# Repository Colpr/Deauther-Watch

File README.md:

# Deauther-Watch
PCB, schematic and image files for the deauther watch project by Colpr on https://hackaday.io/project/193281-deauther-smart-watch-v1

##### Project is currently on version 1.

### NOTE: Please refer to the license, this project is open-source under the MIT license with all the terms and conditions.

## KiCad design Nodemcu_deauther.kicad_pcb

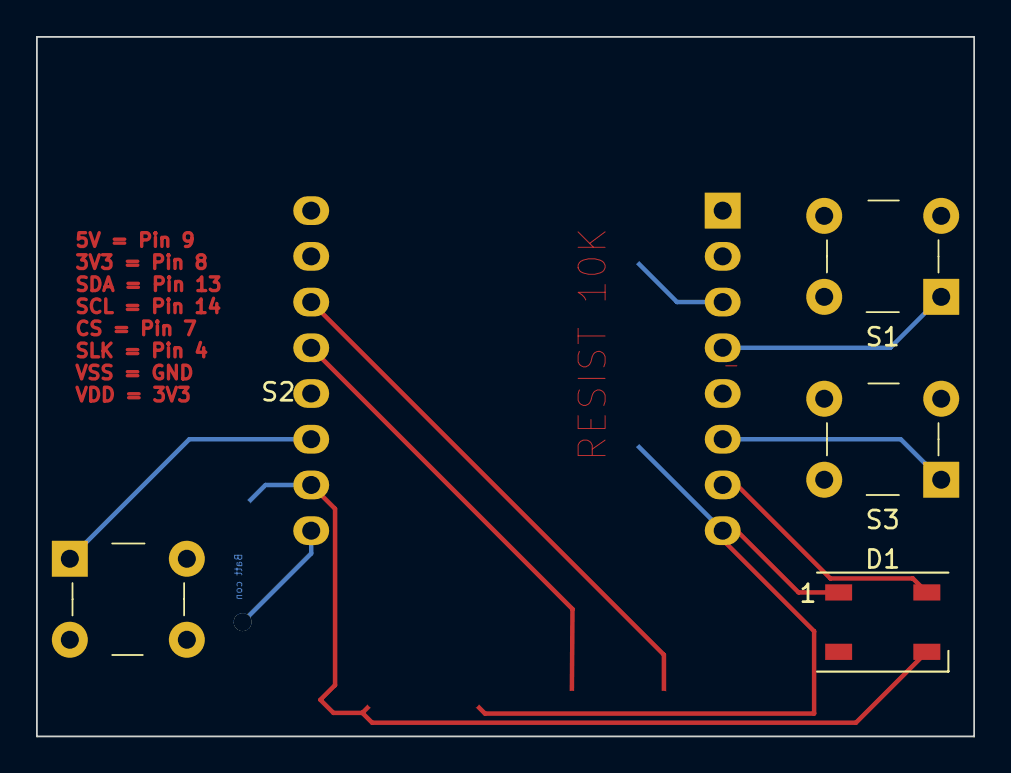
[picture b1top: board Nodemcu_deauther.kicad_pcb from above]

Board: 2 copper layers, 52.1 x 38.9 mm, 5 parts (1 on the bottom side), 6 nets.

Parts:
D1: WS2812B; LED_WS2812B_PLCC4_5.0x5.0mm_P3.2mm
S1, S2, S3: B3F-1000; Switch_Tactile_THT_B3F-1xxx
U1: WeMos_D1_mini; WEMOS_D1_mini_light

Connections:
unnamed: D1.3 (VSS), U1.10 (GND)
unnamed: D1.1 (VDD), U1.8 (3V3)
unnamed: D1.4 (DIN), U1.7 (CS/D8)
unnamed: S2.1, U1.11 (D4)
unnamed: S3.1, U1.6 (MOSI/D7)
unnamed: S1.1, U1.4 (SCK/D5)

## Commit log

2023-10-22 Update LICENSE
